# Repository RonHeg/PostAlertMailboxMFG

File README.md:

# PostAlertMailboxMFG
 PostAlert IoT Mailbox Unit Manufacturing documentation

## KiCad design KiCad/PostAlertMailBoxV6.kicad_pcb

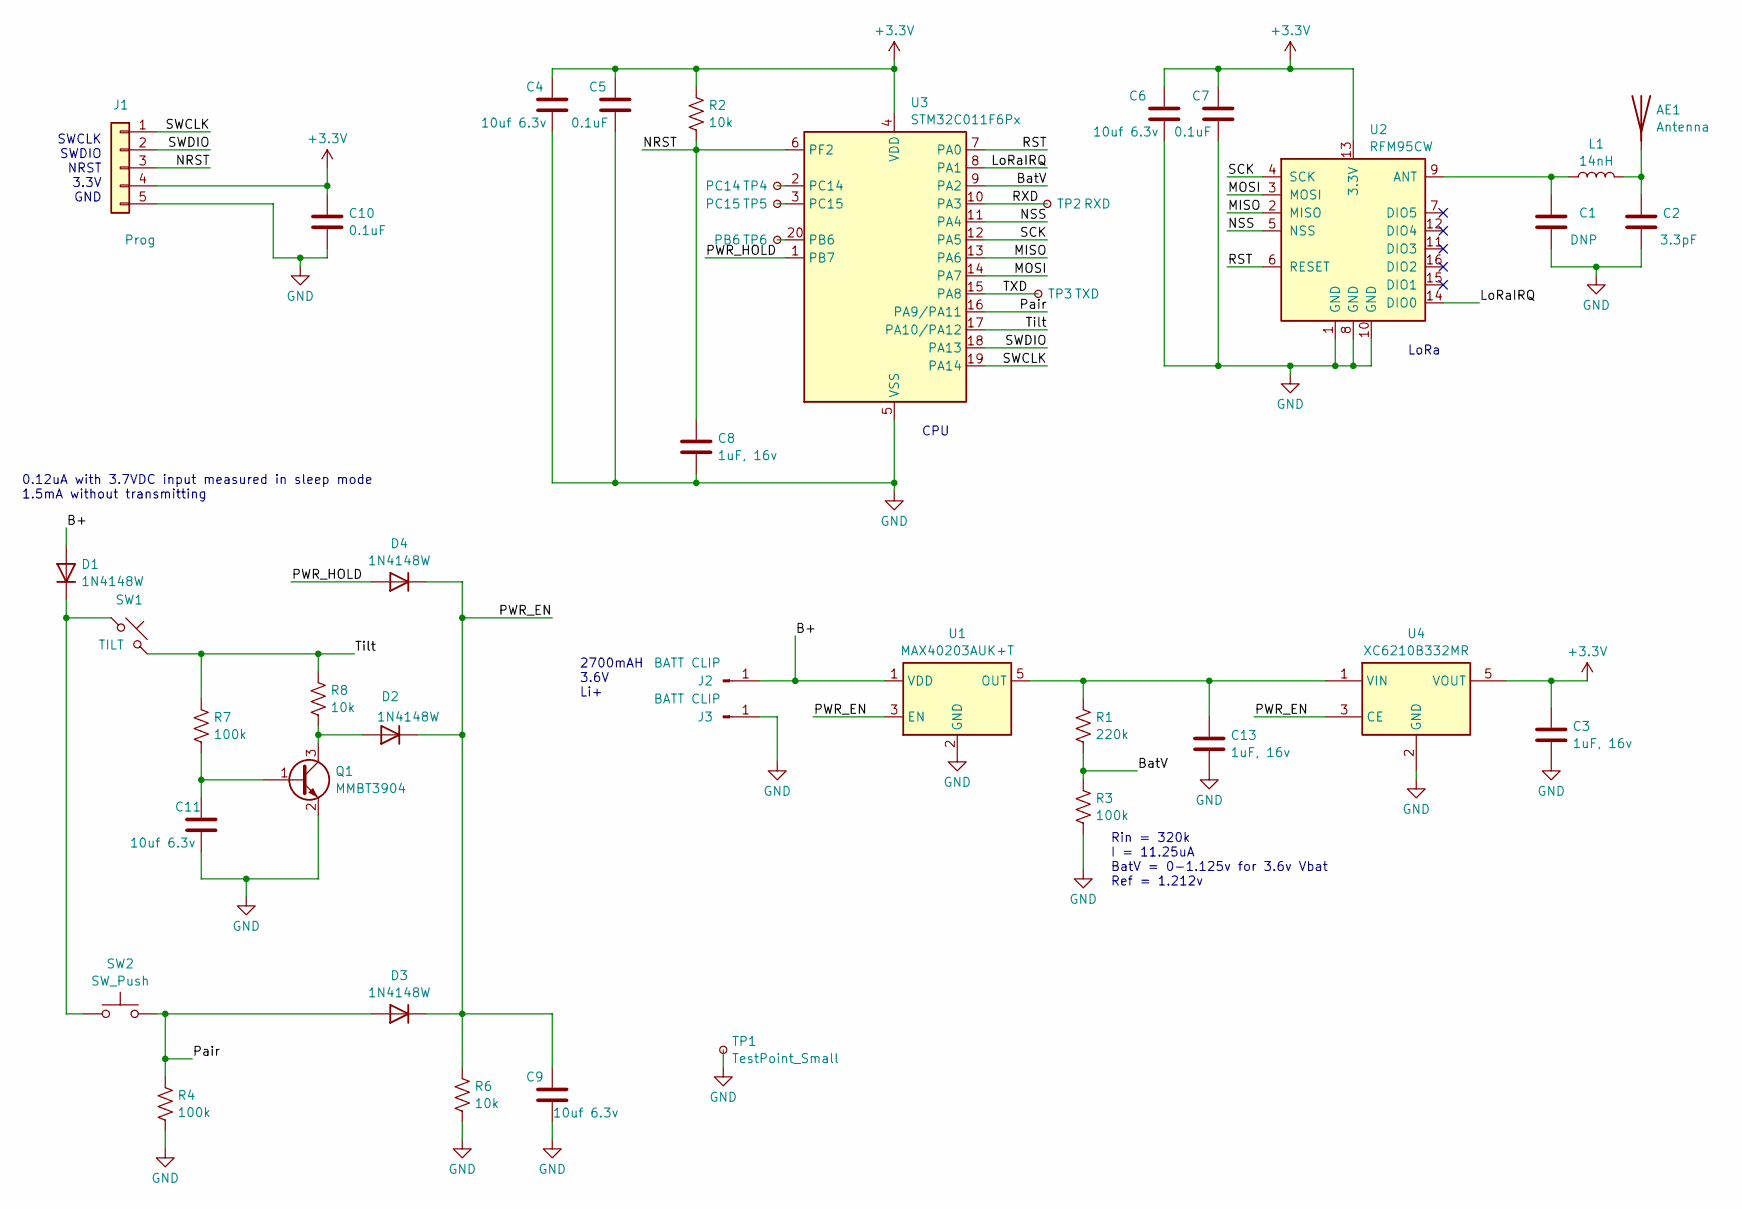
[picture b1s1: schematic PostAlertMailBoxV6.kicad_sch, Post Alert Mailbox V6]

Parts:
AE1: Antenna; Texas_SWRA416_868MHz_915MHz
C1: DNP; C_0603_1608Metric
C2: 3.3pF; C_0603_1608Metric
C3, C8, C13: 1uF, 16v; C_0603_1608Metric
C4, C6, C9, C11: 10uf 6.3v; C_0603_1608Metric
C5, C7, C10: 0.1uF; C_0603_1608Metric
D1, D2, D3, D4: 1N4148W; D_SOD-123
J1: Prog; PinHeader_1x05_P2.54mm_Vertical
J2, J3: BATT CLIP; BatteryClip_Keystone_92_AA-14mm
L1: 14nH; L_0603_1608Metric
Q1: MMBT3904; SOT-23
R1: 220k; R_0603_1608Metric
R2, R6, R8: 10k; R_0603_1608Metric
R3, R4, R7: 100k; R_0603_1608Metric
SW1: TILT; PinHeader_1x02_P2.54mm_Vertical
SW2: SW_Push; SW_Push_1P1T_NO_6x6mm_H9.5mm
TP1: TestPoint_Small; TestPoint_Loop_D2.50mm_Drill1.85mm
TP2: RXD; TestPoint_Pad_D1.0mm
TP3: TXD; TestPoint_Pad_D1.0mm
TP4: PC14; TestPoint_Pad_D1.0mm
TP5: PC15; TestPoint_Pad_D1.0mm
TP6: PB6; TestPoint_Pad_D1.0mm
U1: MAX40203AUK+T; SOT-23-5
U2: RFM95CW; HOPERF_RFM9XW_SMD
U3: STM32C011F6Px; TSSOP-20_4.4x6.5mm_P0.65mm
U4: XC6210B332MR; SOT-23-5

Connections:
+3.3V: C3.1, C4.1, C5.1, C6.1, C7.1, C10.1, J1.4, R2.1, U2.13 (3.3V), U3.4 (VDD), U4.5 (VOUT)
/B+: D1.2 (A), J2.1, U1.1 (VDD)
/BatV: R1.2, R3.1, U3.9 (PA2)
/LoRaIRQ: U2.14 (DIO0), U3.8 (PA1)
/MISO: U2.2 (MISO), U3.13 (PA6)
/MOSI: U2.3 (MOSI), U3.14 (PA7)
/NRST: C8.1, J1.3, R2.2, U3.6 (PF2)
/NSS: U2.5 (NSS), U3.11 (PA4)
/PWR_EN: C9.1, D2.1 (K), D3.1 (K), D4.1 (K), R6.1, U1.3 (EN), U4.3 (CE)
/PWR_HOLD: D4.2 (A), U3.1 (PB7)
/Pair: D3.2 (A), R4.1, SW2.1, U3.16 (PA9/PA11)
/RST: U2.6 (RESET), U3.7 (PA0)
/RXD: TP2.1, U3.10 (PA3)
/SCK: U2.4 (SCK), U3.12 (PA5)
/SWCLK: J1.1, U3.19 (PA14)
/SWDIO: J1.2, U3.18 (PA13)
/TXD: TP3.1, U3.15 (PA8)
/Tilt: R7.1, R8.1, SW1.2, U3.17 (PA10/PA12)
GND: C1.2, C2.2, C3.2, C4.2, C5.2, C6.2, C7.2, C8.2, C9.2, C10.2, C11.2, C13.2, J1.5, J3.1, Q1.2 (E), R3.2, R4.2, R6.2, TP1.1, U1.2 (GND), U2.1 (GND), U2.8 (GND), U2.10 (GND), U3.5 (VSS), U4.2 (GND)
unnamed: AE1.1 (A), C2.1, L1.2
unnamed: D1.1 (K), SW1.1, SW2.2
unnamed: D2.2 (A), Q1.3 (C), R8.2
unnamed: C11.1, Q1.1 (B), R7.2
unnamed: C13.1, R1.1, U1.5 (OUT), U4.1 (VIN)
unnamed: C1.1, L1.1, U2.9 (ANT)
unnamed: TP6.1, U3.20 (PB6)
unnamed: TP4.1, U3.2 (PC14)
unnamed: TP5.1, U3.3 (PC15)

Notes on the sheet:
SWCLK SWDIO NRST 3.3V GND
0.12uA with 3.7VDC input measured in sleep mode 1.5mA without transmitting
LoRa
2700mAH 3.6V Li+
Rin = 320k I = 11.25uA BatV = 0-1.125v for 3.6v Vbat Ref = 1.212v
CPU

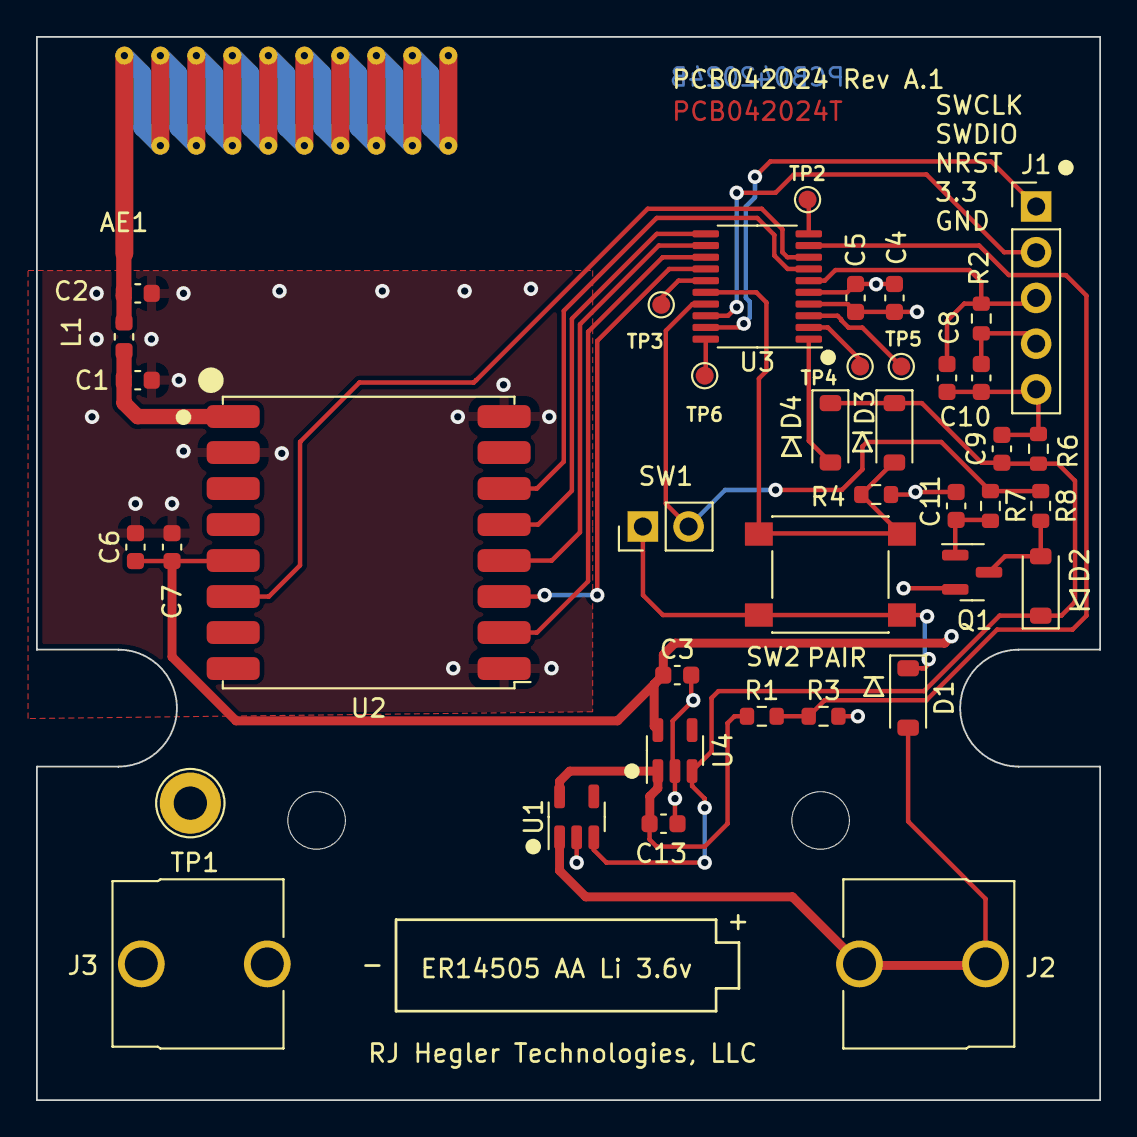
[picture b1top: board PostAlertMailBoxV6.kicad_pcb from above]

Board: 2 copper layers, 59.1 x 59.1 mm, 41 parts (0 on the bottom side), 28 nets.

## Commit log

2025-02-27 Initial File Upload
    Initial file upload 2/27/2025
